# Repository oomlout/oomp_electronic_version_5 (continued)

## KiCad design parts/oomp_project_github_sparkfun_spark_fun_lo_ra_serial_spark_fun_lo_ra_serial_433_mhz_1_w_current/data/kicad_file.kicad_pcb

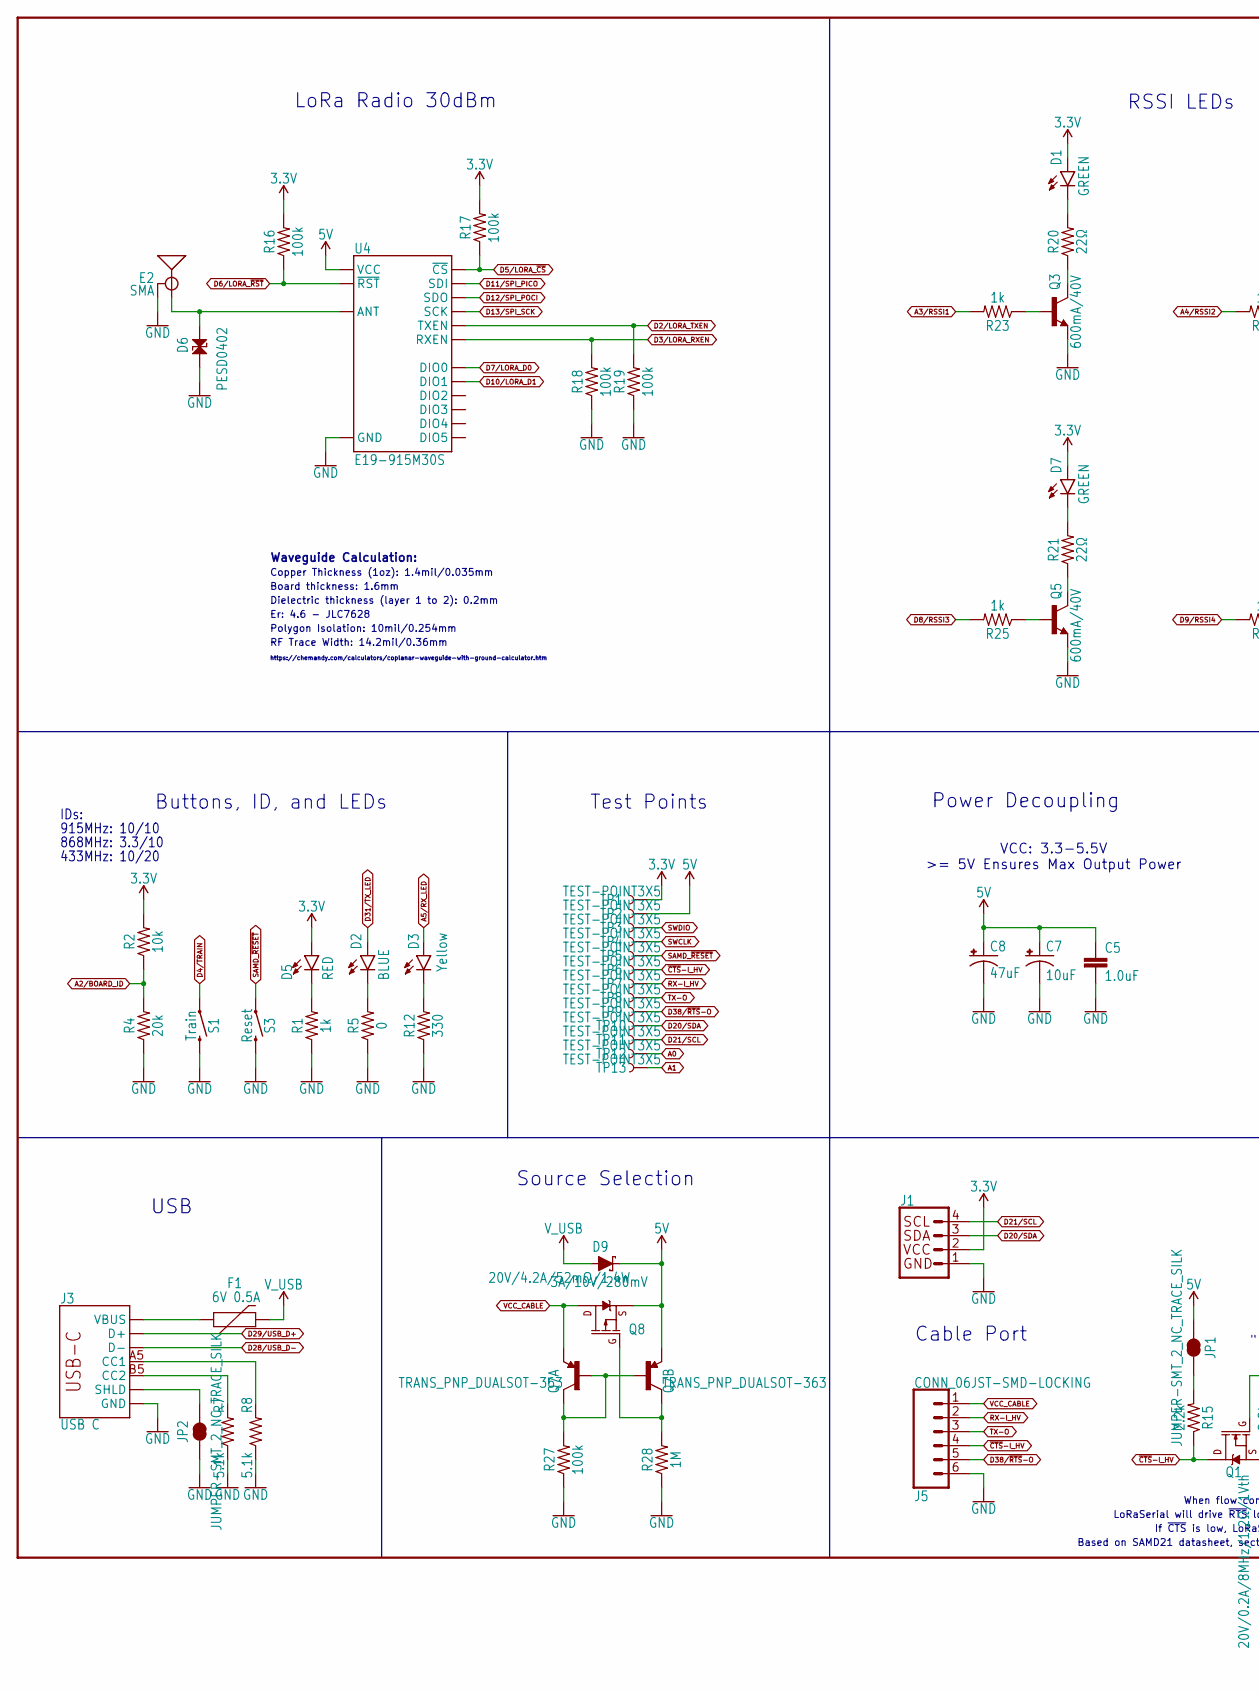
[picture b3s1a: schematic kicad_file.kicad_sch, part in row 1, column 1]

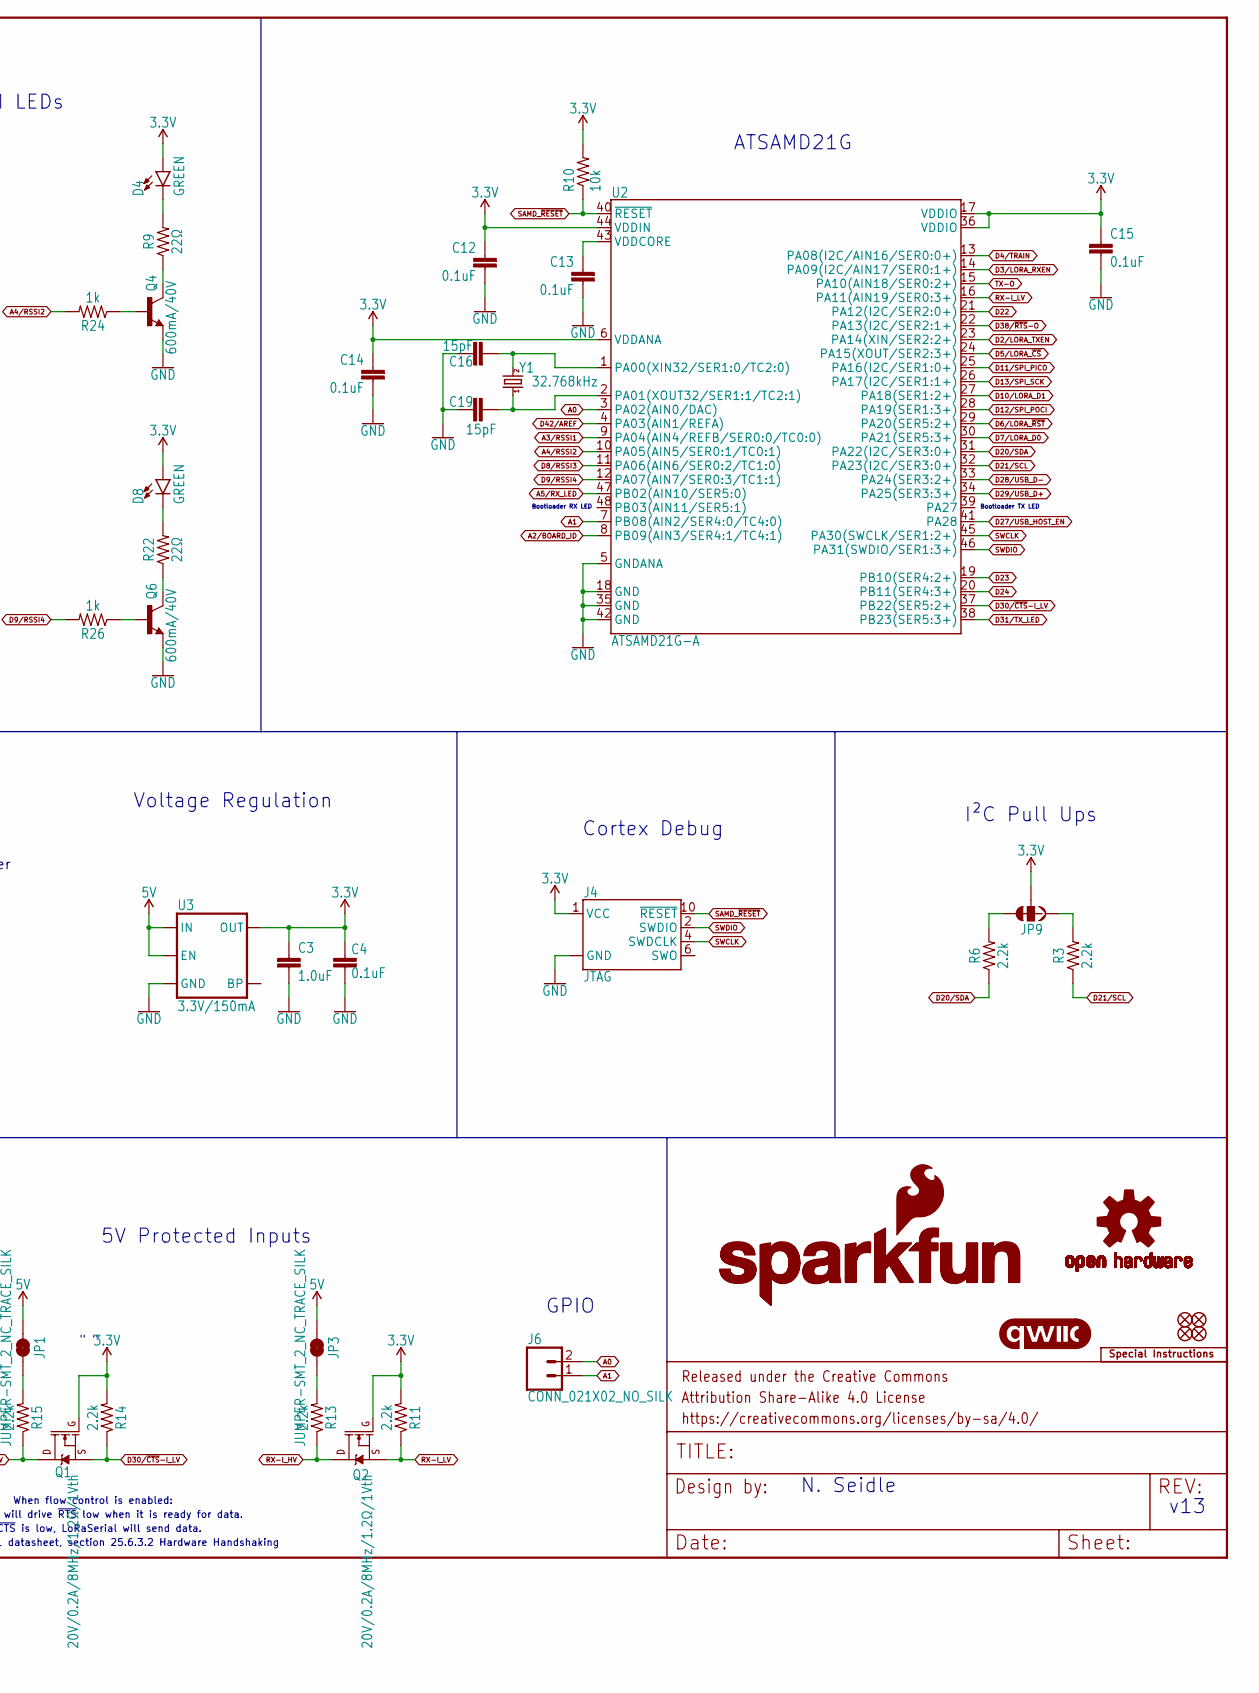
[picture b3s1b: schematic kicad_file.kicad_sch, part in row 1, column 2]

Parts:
C3, C5: 1.0uF; 0603
C4, C12, C13, C14, C15: 0.1uF; 0603
C7: 10uF; EIA3216
C8: 47uF; EIA3528
C16, C19: 15pF; 0603
D1, D4, D7, D8: GREEN; LED-0603
D2: BLUE; LED-0603
D3: Yellow; LED-0603
D5: RED; LED-0603
D6: PESD0402; 0402-TIGHT
D9: 3A/10V/280mV; SOD-323
E2: SMA; SMA-EDGE
F1: 6V 0.5A; 0805
FID1, FID2, FID3, FID4: FIDUCIAL1X2; FIDUCIAL-1X2
FRAME3: FRAME-LEDGER; CREATIVE_COMMONS
J1: QWIIC_RIGHT_ANGLE; JST04_1MM_RA
J3: USB C; USB-C-16P
J4: JTAG; 2X5-PTH-1.27MM-NO_SILK
J5: CONN_06JST-SMD-LOCKING; JST-6-SMD-1.25MM-LOCKING
J6: CONN_021X02_NO_SILK; 1X02_NO_SILK
JP1, JP2, JP3: JUMPER-SMT_2_NC_TRACE_SILK; SMT-JUMPER_2_NC_TRACE_SILK
JP9: JUMPER-SMT_3_2-NC_TRACE_SILK; SMT-JUMPER_3_2-NC_TRACE_SILK
LOGO1: SPECIAL_INSTRUCTIONS-ORDERING; ORDERING_INSTRUCTIONS
LOGO2: SFE_LOGO_NAME_FLAME9_MM; SFE_LOGO_NAME_FLAME_9MM
LOGO3: QWIIC_LOGO_CONNECTOR; QWIIC_5.5MM
LOGO4: OSHW-LOGOMINI; OSHW-LOGO-MINI
LOGO5: SFE_LOGO_NAME9_MM; SFE_LOGO_NAME_9MM
Q1, Q2: 20V/0.2A/8MHz/1.2Ω/1Vth; SOT-416FL
Q3, Q4, Q5, Q6: 600mA/40V; SOT23-3
Q7: TRANS_PNP_DUALSOT-363; SOT363_PHILIPS
Q8: 20V/4.2A/52mΩ/1.4W; SOT23-3
R1, R23, R24, R25, R26: 1k; 0603
R2, R10: 10k; 0603
R3, R6, R11, R13, R14, R15: 2.2k; 0603
R4: 20k; 0603
R5: 0; 0603
R7, R8: 5.1k; 0603
R9, R20, R21, R22: 22Ω; 0603
R12: 330; 0603
R16, R17, R18, R19, R27: 100k; 0603
R28: 1M; 0603
S1: Train; TACTILE_SWITCH_SMD_RIGHT_ANGLE
S3: Reset; TACTILE_SWITCH_SMD_5.2MM
TP1, TP2, TP3, TP4, TP5, TP6, TP7, TP8, TP9, TP10, TP11, TP12, TP13: TEST-POINT3X5; PAD.03X.05
U2: ATSAMD21G-A; TQFP-48
U3: 3.3V/150mA; SOT23-5
U4: E19-915M30S; E19-433M30S
Y1: 32.768kHz; CRYSTAL-SMD-3.2X1.5MM

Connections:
3.3V: C3.1, C4.2, C12.1, C14.1, C15.1, D1.A, D4.A, D5.A, D7.A, D8.A, J1.2, J4.1 (VCC), JP9.2, Q1.1 (G), Q2.1 (G), R2.2, R10.2, R11.2, R14.2, R16.2, R17.2, TP1.1, U2.6 (VDDANA), U2.17 (VDDIO), U2.36 (VDDIO), U2.44 (VDDIN), U3.5 (OUT)
5V: C5.1, C7.+, C8.A (+), D9.C, JP1.2, JP3.2, Q7.4 (E), Q8.2 (S), TP2.1, U3.1 (IN), U3.3 (EN), U4.11 (VCC)
A0: J6.2, TP12.1, U2.3 (PA02(AIN0/DAC))
A1: J6.1, TP13.1, U2.7 (PB08(AIN2/SER4:0/TC4:0))
A2/BOARD_ID: R2.1, R4.2, U2.8 (PB09(AIN3/SER4:1/TC4:1))
A3/RSSI1: R23.2, U2.9 (PA04(AIN4/REFB/SER0:0/TC0:0))
A4/RSSI2: R24.2, U2.10 (PA05(AIN5/SER0:1/TC0:1))
A5/RX_LED: D3.A, U2.47 (PB02(AIN10/SER5:0))
CC1: J3.A5 (CC1), R8.2
CC2: J3.B5 (CC2), R7.2
D2/LORA_TXEN: R19.2, U2.23 (PA14(XIN/SER2:2+)), U4.16 (TXEN)
D3/LORA_RXEN: R18.2, U2.14 (PA09(I2C/AIN17/SER0:1+)), U4.17 (RXEN)
D4/TRAIN: S1.1, U2.13 (PA08(I2C/AIN16/SER0:0+))
D5/LORA_~CS: R17.1, U2.24 (PA15(XOUT/SER2:3+)), U4.15 (~CS)
D6/LORA_~RST: R16.1, U2.29 (PA20(SER5:2+)), U4.8 (~RST)
D7/LORA_D0: U2.30 (PA21(SER5:3+)), U4.7 (DIO0)
D8/RSSI3: R25.2, U2.11 (PA06(AIN6/SER0:2/TC1:0))
D9/RSSI4: R26.2, U2.12 (PA07(AIN7/SER0:3/TC1:1))
D10/LORA_D1: U2.27 (PA18(SER1:2+)), U4.6 (DIO1)
D11/SPI_PICO: U2.25 (PA16(I2C/SER1:0+)), U4.14 (SDI)
D12/SPI_POCI: U2.28 (PA19(SER1:3+)), U4.13 (SDO)
D13/SPI_SCK: U2.26 (PA17(I2C/SER1:1+)), U4.12 (SCK)
D20/SDA: J1.3, R6.1, TP10.1, U2.31 (PA22(I2C/SER3:0+))
D21/SCL: J1.4, R3.1, TP11.1, U2.32 (PA23(I2C/SER3:0+))
D22: U2.21 (PA12(I2C/SER2:0+))
D23: U2.19 (PB10(SER4:2+))
D24: U2.20 (PB11(SER4:3+))
D27/USB_HOST_EN: U2.41 (PA28)
D28/USB_D-: J3.A7 (D-), J3.B7 (D-), U2.33 (PA24(SER3:2+))
D29/USB_D+: J3.A6 (D+), J3.B6 (D+), U2.34 (PA25(SER3:3+))
D30/~CTS-I_LV: Q1.2 (S), R14.1, U2.37 (PB22(SER5:2+))
D31/TX_LED: D2.A, U2.38 (PB23(SER5:3+))
D38/~RTS-O: J5.5, TP9.1, U2.22 (PA13(I2C/SER2:1+))
D42/AREF: U2.4 (PA03(AIN1/REFA))
GND: C3.2, C4.1, C5.2, C7.-, C8.C (-), C12.2, C13.2, C14.2, C15.2, C16.1, C19.2, D6.1, E2.GND@0 (GND), E2.GND@1 (GND), E2.GND@2 (GND), E2.GND@3 (GND), J1.1, J3.GND, J3.GND2 (GND), J4.3 (GND), J4.5 (GND), J4.9 (GND), J5.6, JP2.1, Q3.2 (E), Q4.2 (E), Q5.2 (E), Q6.2 (E), R1.1, R4.1, R5.1, R7.1, R8.1, R12.1, R18.1, R19.1, R27.1, R28.1, S1.2, S3.3 (2), S3.4 (2), U2.5 (GNDANA), U2.18 (GND), U2.35 (GND), U2.42 (GND), U3.2 (GND), U4.1 (GND), U4.9 (GND), U4.10 (GND), U4.18 (GND), U4.20 (GND), U4.21 (GND), U4.22 (GND)
LORA_ANT: D6.2, E2.SIG (SIGNAL), U4.19 (ANT)
unnamed: C19.1, U2.2 (PA01(XOUT32/SER1:1/TC2:1)), Y1.P$1 (1)
unnamed: C16.2, U2.1 (PA00(XIN32/SER1:0/TC2:0)), Y1.P$2 (2)
unnamed: D3.C, R12.2
unnamed: D2.C, R5.2
unnamed: JP3.1, R13.2
unnamed: JP1.1, R15.2
unnamed: D5.C, R1.2
unnamed: D4.C, R9.2
unnamed: D1.C, R20.2
unnamed: D7.C, R21.2
unnamed: D8.C, R22.2
unnamed: Q3.3 (C), R20.1
unnamed: Q3.1 (B), R23.1
unnamed: Q4.3 (C), R9.1
unnamed: Q4.1 (B), R24.1
unnamed: Q5.3 (C), R21.1
unnamed: Q5.1 (B), R25.1
unnamed: Q6.3 (C), R22.1
unnamed: Q6.1 (B), R26.1
unnamed: J3.SHLD1 (SHLD), J3.SHLD2 (SHLD), J3.SHLD3 (SHLD), J3.SHLD4 (SHLD), J3.SHLD5 (SHLD), J3.SHLD6 (SHLD), J3.SHLD7 (SHLD), J3.SHLD8 (SHLD), JP2.2
unnamed: Q7.3 (C), Q8.1 (G), R28.2
unnamed: Q7.2 (B), Q7.5 (B), Q7.6 (C), R27.2
RX-I_HV: J5.2, Q2.3 (D), R13.1, TP7.1
RX-I_LV: Q2.2 (S), R11.1, U2.16 (PA11(AIN19/SER0:3+))
SAMD_~RESET: J4.10 (~RESET), R10.1, S3.1, S3.2 (1), TP5.1, U2.40 (~RESET)
SCL_PU1: JP9.1, R3.2
SDA_PU1: JP9.3, R6.2
SWCLK: J4.4 (SWDCLK), TP4.1, U2.45 (PA30(SWCLK/SER1:2+))
SWDIO: J4.2 (SWDIO), TP3.1, U2.46 (PA31(SWDIO/SER1:3+))
TX-O: J5.3, TP8.1, U2.15 (PA10(AIN18/SER0:2+))
VCC_CABLE: J5.1, Q7.1 (E), Q8.3 (D)
VDDCORE: C13.1, U2.43 (VDDCORE)
VUSB: F1.1, J3.VBUS1 (VBUS), J3.VBUS2 (VBUS)
V_USB: D9.A, F1.2
~CTS-I_HV: J5.4, Q1.3 (D), R15.1, TP6.1

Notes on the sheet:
ATSAMD21G
Er: 4.6 - JLC7628
Buttons, ID, and LEDs
https://chemandy.com/calculators/coplanar-waveguide-with-ground-calculator.htm
Voltage Regulation
LoRaSerial will drive ~{RTS} low when it is ready for data.
Cable Port
Power Decoupling
N. Seidle
Based on SAMD21 datasheet, section 25.6.3.2 Hardware Handshaking
I²C Pull Ups
When flow control is enabled:
Dielectric thickness (layer 1 to 2): 0.2mm
v13
RSSI LEDs
RF Trace Width: 14.2mil/0.36mm
LoRa Radio 30dBm
Copper Thickness (1oz): 1.4mil/0.035mm
USB
Bootloader TX LED
Bootloader RX LED
433MHz: 10/20
GPIO
Polygon Isolation: 10mil/0.254mm
Source Selection
VCC: 3.3-5.5V >= 5V Ensures Max Output Power
915MHz: 10/10
Test Points
Cortex Debug
Waveguide Calculation:
" "
Board thickness: 1.6mm
If ~{CTS} is low, LoRaSerial will send data.
IDs:
5V Protected Inputs
868MHz: 3.3/10

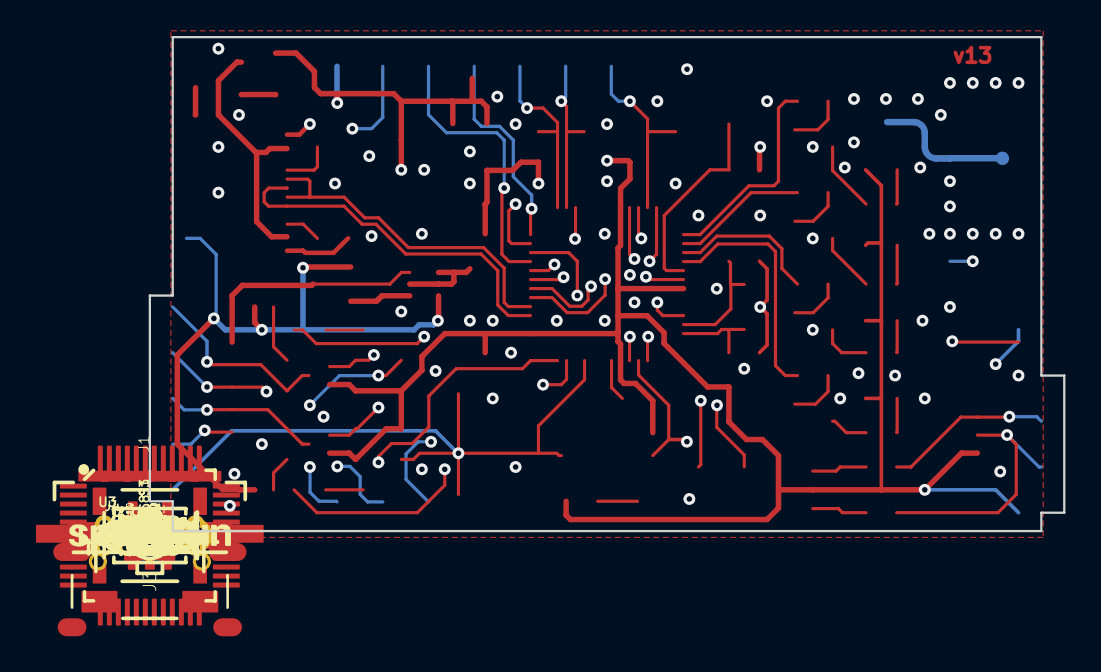
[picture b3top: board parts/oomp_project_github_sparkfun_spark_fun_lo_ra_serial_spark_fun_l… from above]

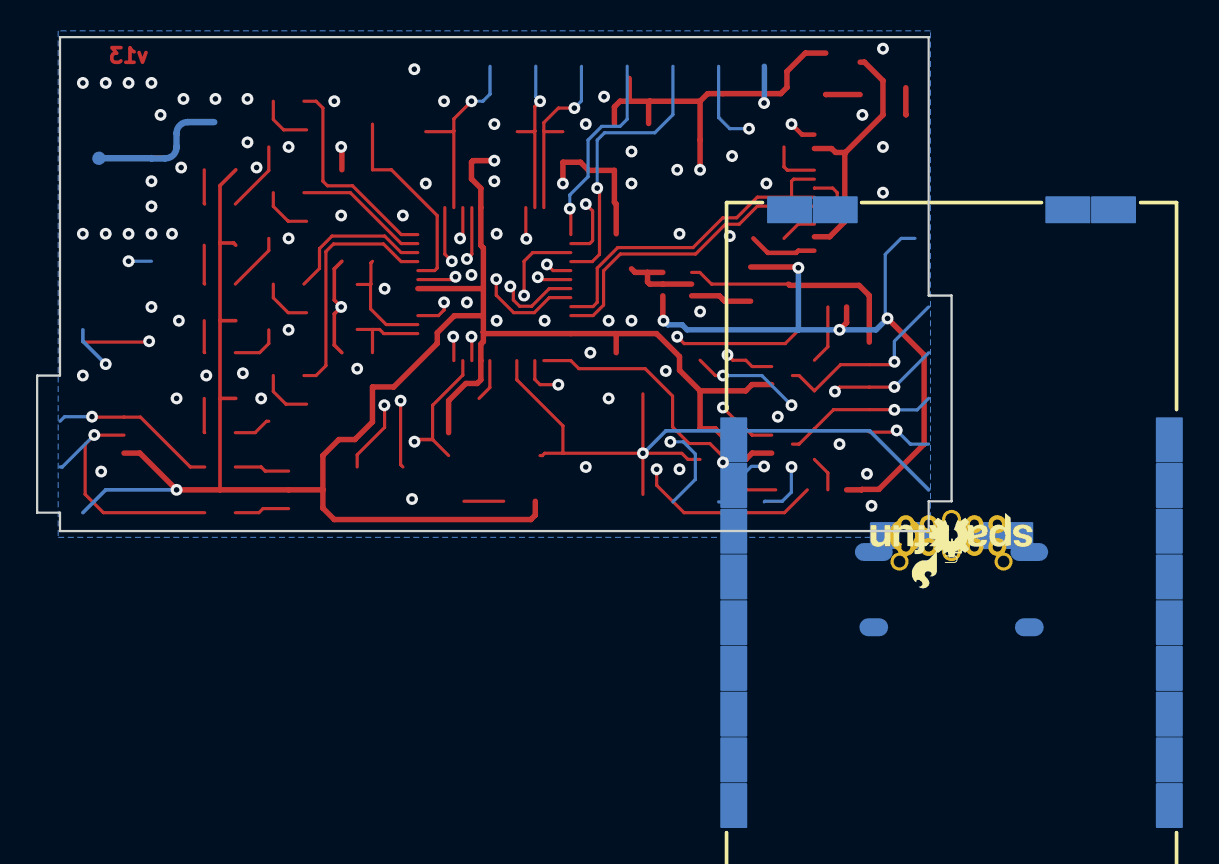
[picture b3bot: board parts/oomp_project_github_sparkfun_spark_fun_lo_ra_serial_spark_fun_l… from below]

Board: 4 copper layers, 50.8 x 27.4 mm, 118 parts (20 on the bottom side), 66 nets.

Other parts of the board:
U$1: 1W1
U$2: RESET0
U$4: TRAIN0
U$5: RADIO2
U$6: 01
U$7: PWR0
U$8: 433MHZ0
U$9: ANTENNA1
U$10: RX1
U$11: TX0
U$12: #0
U$13: #1
U$14: R3
U$15: T2
U$16: C0
U$17: R1
U$18: LORASERIAL0
U$19: C50
U$20: R50
U$21: RSSI0
U$22: 10
U$23: SH0

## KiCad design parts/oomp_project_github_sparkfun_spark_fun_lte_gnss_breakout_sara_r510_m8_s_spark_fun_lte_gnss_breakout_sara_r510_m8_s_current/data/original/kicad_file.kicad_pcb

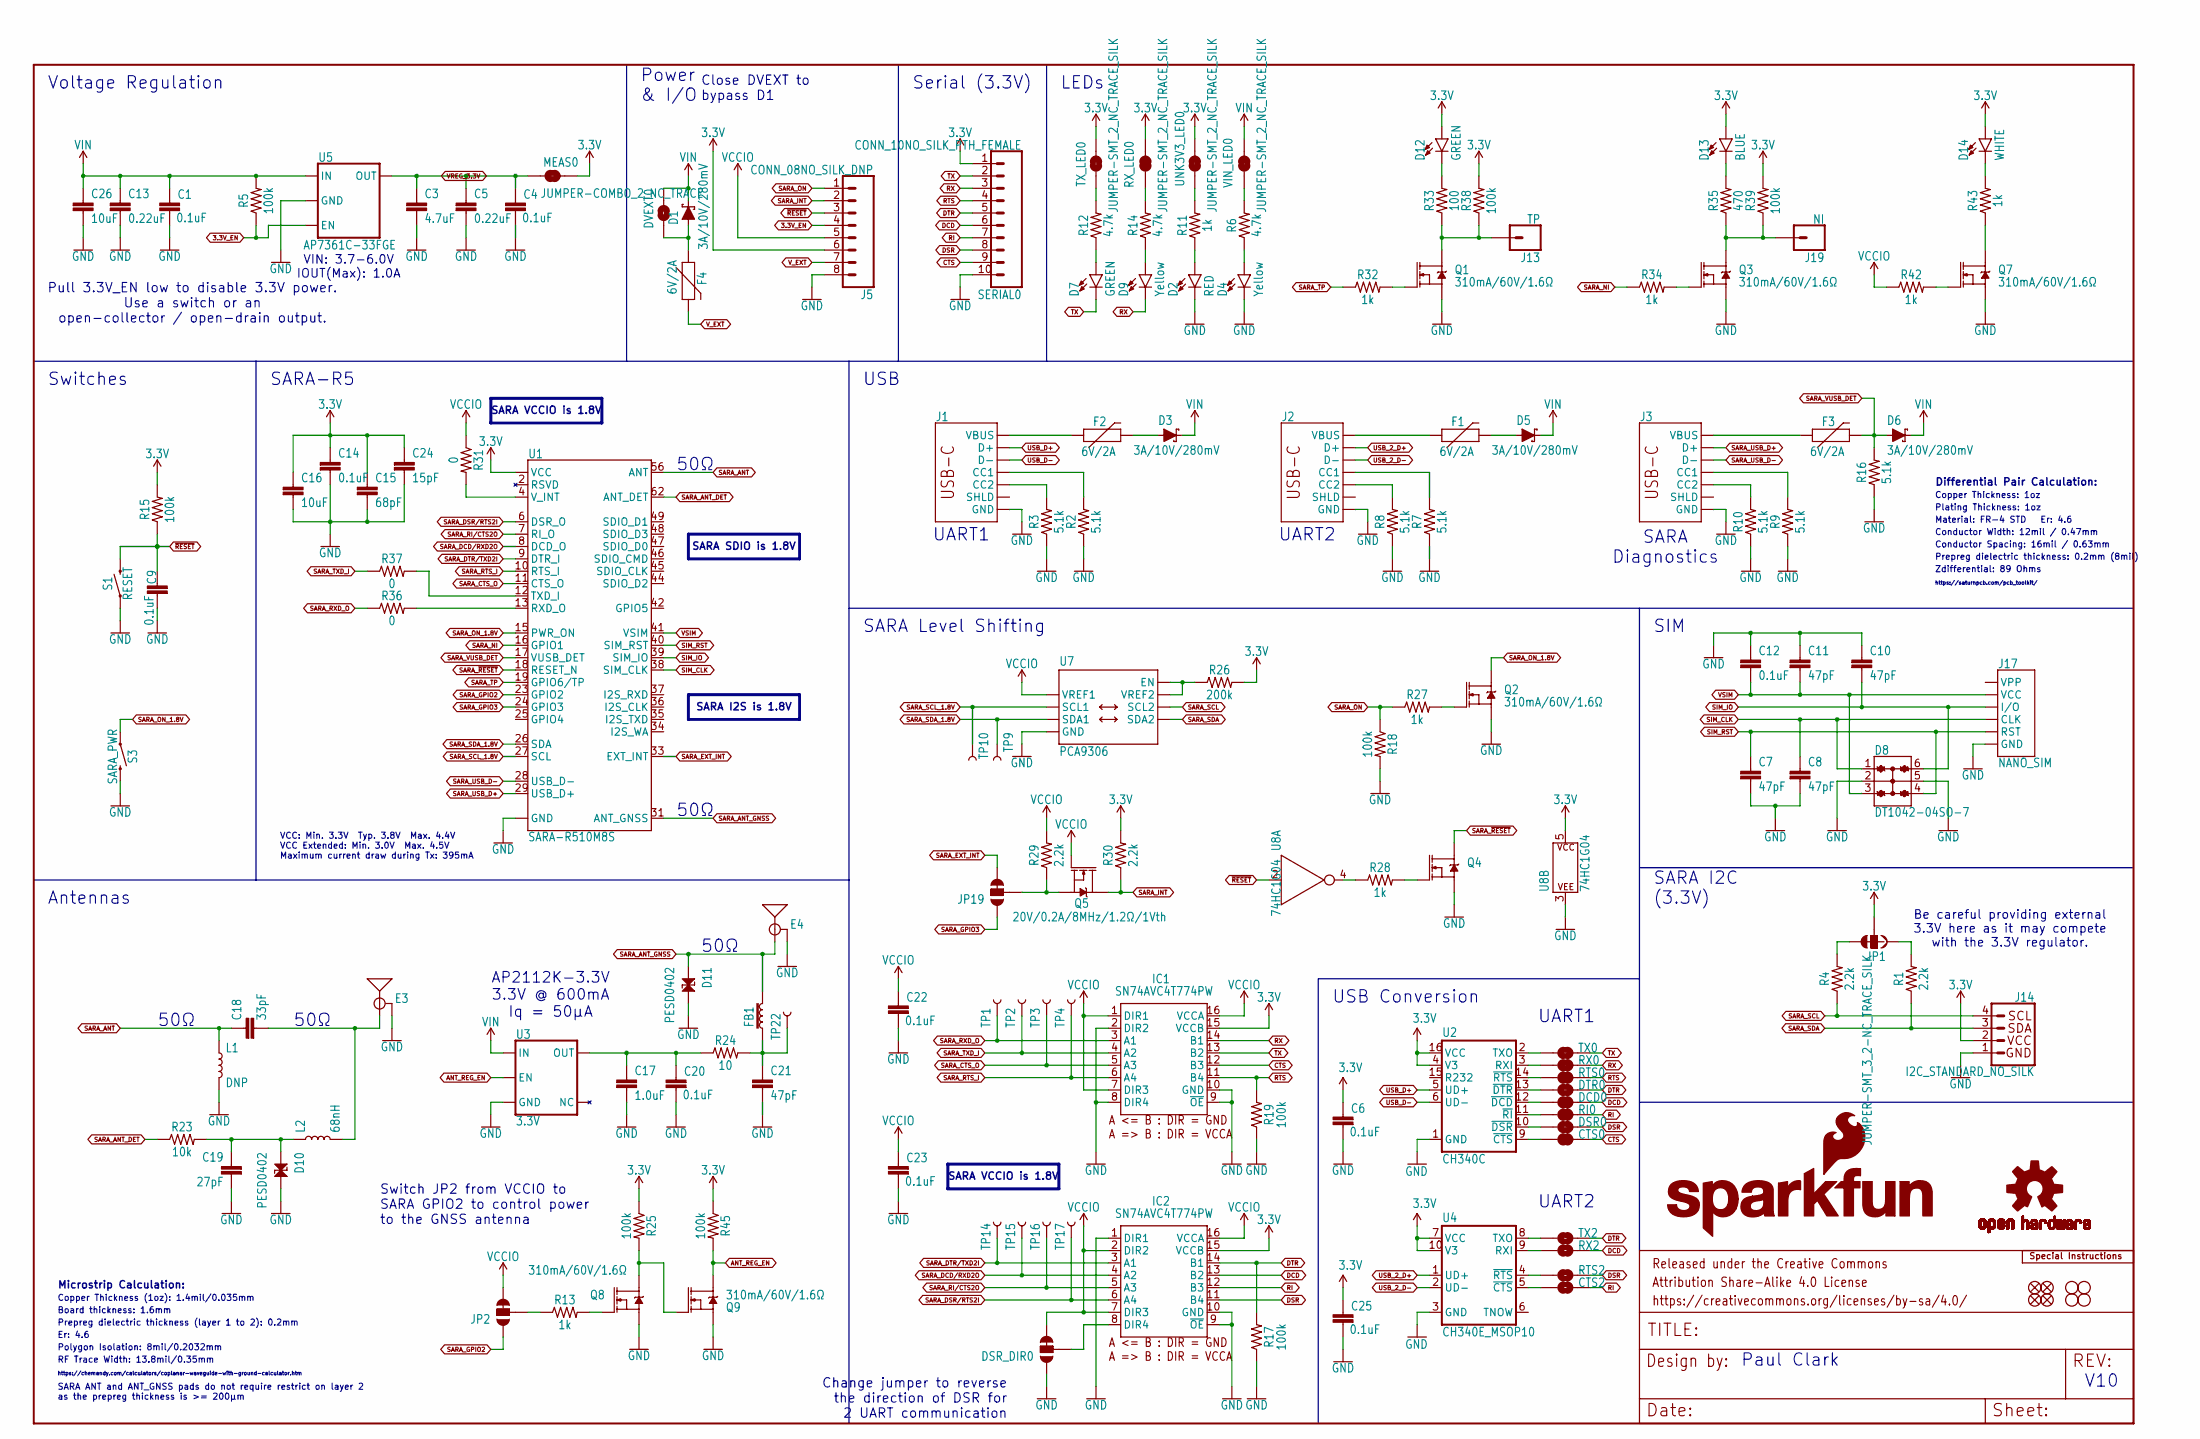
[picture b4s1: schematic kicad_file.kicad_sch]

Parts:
C1, C4, C6, C9, C12, C14, C20, C22, C23, C25: 0.1uF; 0603
C3: 4.7uF; 0603
C5, C13: 0.22uF; 0603
C7, C8, C10, C11, C21: 47pF; 0603
C15: 68pF; 0603
C16: 10uF; 0603
C17: 1.0uF; 0603
C18: 33pF; 0402-TIGHT
C19: 27pF; 0402
C24: 15pF; 0603
C26: 10uF; 0805
CTS0: JUMPER-SMT_2_NC_TRACE_SILK; SMT-JUMPER_2_NC_TRACE_SILK
CTS2: JUMPER-SMT_2_NO_SILK; SMT-JUMPER_2_NO_SILK
D1, D3, D5, D6: 3A/10V/280mV; SOD-323
D2: RED; LED-0603
D4, D9: Yellow; LED-0603
D7, D12: GREEN; LED-0603
D8: DT1042-04SO-7; SOT23-6L
D10, D11: PESD0402; 0402; MOUSE_PART 650-PESD0402-140; DIGIKEY_PART PESD0402-140CT-ND
D13: BLUE; LED-0603
D14: WHITE; LED-0603
DCD0: JUMPER-SMT_2_NC_TRACE_SILK; SMT-JUMPER_2_NC_TRACE_SILK
DSR0: JUMPER-SMT_2_NC_TRACE_SILK; SMT-JUMPER_2_NC_TRACE_SILK
DSR_DIR0: JUMPER-SMT_3_1-NC_TRACE_SILK; SMT-JUMPER_3_1-NC_TRACE_SILK
DTR0: JUMPER-SMT_2_NC_TRACE_SILK; SMT-JUMPER_2_NC_TRACE_SILK
DVEXT0: JUMPER-SMT_2_NO_SILK; SMT-JUMPER_2_NO_SILK
E3, E4: ANTENNA-SMA-GROUNDEDEDGE_SMA_SMD; SMA-EDGE-SMD
F1, F2, F3, F4: 6V/2A; 1210
FB1: 30Ω/1.8A; 0603
FD1, FD2, FD3, FD4: FIDUCIALUFIDUCIAL; FIDUCIAL-MICRO
FRAME1: FRAME-LEDGER; CREATIVE_COMMONS
H1, H2, H3, H4: STAND-OFF
IC1, IC2: SN74AVC4T774PW; SOP65P640X120-16N
J1, J2, J3: USB_C_4-LAYER_PADS; USB-C-16P_4LAYER-PADS
J5: CONN_08NO_SILK_DNP; 1X08_NO_SILK
J13: TP; 1X01_NO_SILK
J14: I2C_STANDARD_NO_SILK; 1X04_NO_SILK
J17: NANO_SIM; NANO_SIM_WURTH_693043020611
J19: NI; 1X01_NO_SILK
JP1: JUMPER-SMT_3_2-NC_TRACE_SILK; SMT-JUMPER_3_2-NC_TRACE_SILK
JP2, JP19: JUMPER-SMT_3_1-NC_TRACE_SILK; SMT-JUMPER_3_1-NC_TRACE_SILK
L1: DNP; 0402_COILCRAFT
L2: 68nH; 0402_COILCRAFT; MOUSER_PART 81-LQG15HS68NJ02D; DIGIKEY_PART 490-2633-1-ND
LOGO1: SFE_LOGO_NAME_FLAME.1_INCH; SFE_LOGO_NAME_FLAME_.1
LOGO3: OSHW-LOGOMINI; OSHW-LOGO-MINI
LOGO5: SPECIAL_INSTRUCTIONS-ORDERING; ORDERING_INSTRUCTIONS
MEAS0: JUMPER-COMBO_2_NC_TRACE; COMBO-JUMPER_2_NC_TRACE
Q1, Q2, Q3, Q4, Q7, Q8, Q9: 310mA/60V/1.6Ω; SOT323
Q5: 20V/0.2A/8MHz/1.2Ω/1Vth; SOT-416FL
R1, R4, R29, R30: 2.2k; 0603
R2, R3, R7, R8, R9, R10, R16: 5.1k; 0603
R5, R15, R17, R18, R19, R25, R38, R39, R45: 100k; 0603
R6, R12, R14: 4.7k; 0603
R11, R13, R27, R28, R32, R34, R42, R43: 1k; 0603
R23: 10k; 0603
R24: 10; 0603
R26: 200k; 0603
R31, R36, R37: 0; 0603
R33: 100; 0603
R35: 470; 0603
RI0: JUMPER-SMT_2_NC_TRACE_SILK; SMT-JUMPER_2_NC_TRACE_SILK
RTS0: JUMPER-SMT_2_NC_TRACE_SILK; SMT-JUMPER_2_NC_TRACE_SILK
RTS2: JUMPER-SMT_2_NO_SILK; SMT-JUMPER_2_NO_SILK
RX0: JUMPER-SMT_2_NC_TRACE_SILK; SMT-JUMPER_2_NC_TRACE_SILK
RX2: JUMPER-SMT_2_NO_SILK; SMT-JUMPER_2_NO_SILK
RX_LED0: JUMPER-SMT_2_NC_TRACE_SILK; SMT-JUMPER_2_NC_TRACE_SILK
S1: RESET; TACTILE_SWITCH_SMD_5.2MM
S3: SARA_PWR; TACTILE_SWITCH_SMD_5.2MM
SERIAL0: CONN_10NO_SILK_PTH_FEMALE; 1X10_NO_SILK
TP1, TP2, TP3, TP4, TP9, TP10, TP14, TP15, TP16, TP17, TP22: TEST-POINT3; PAD.03X.03
TX0: JUMPER-SMT_2_NC_TRACE_SILK; SMT-JUMPER_2_NC_TRACE_SILK
TX2: JUMPER-SMT_2_NO_SILK; SMT-JUMPER_2_NO_SILK
TX_LED0: JUMPER-SMT_2_NC_TRACE_SILK; SMT-JUMPER_2_NC_TRACE_SILK
U1: SARA-R510M8S; SARA-LGA
U2: CH340C; SO016
U3: 3.3V; SOT23-5
U4: CH340E_MSOP10; MSOP10
U5: AP7361C-33FGE; UDFN-8
U7: PCA9306; VSSOP_8PIN
U8: 74HC1G04; SOT353
UNK3V3_LED0: JUMPER-SMT_2_NC_TRACE_SILK; SMT-JUMPER_2_NC_TRACE_SILK
VIN_LED0: JUMPER-SMT_2_NC_TRACE_SILK; SMT-JUMPER_2_NC_TRACE_SILK

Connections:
3.3V: C6.1, C14.1, C15.1, C16.1, C24.1, C25.1, D12.A, D13.A, D14.A, IC1.15 (VCCB), IC2.15 (VCCB), J5.6, J14.2, JP1.2, MEAS0.2, MEAS0.4 (2), R15.2, R25.1, R26.2, R30.2, R38.2, R39.2, R45.1, RX_LED0.2, SERIAL0.1, TX_LED0.2, U1.51 (VCC), U1.52 (VCC), U1.53 (VCC), U2.4 (V3), U2.16 (VCC), U4.7 (VCC), U4.10 (V3), U8.5 (P$V+), UNK3V3_LED0.2
3.3V_EN: J5.4, R5.1, U5.5 (EN)
ANT_REG_EN: Q9.3 (D), R45.2, U3.3 (EN)
CTS: CTS0.2, IC1.12 (B3), SERIAL0.9
DCD: DCD0.2, IC2.13 (B2), RX2.2, SERIAL0.6
DSR: DSR0.2, IC2.11 (B4), RTS2.2, SERIAL0.8
DTR: DTR0.2, IC2.14 (B1), R17.2, SERIAL0.5, TX2.2
GND: C1.2, C3.2, C4.2, C5.2, C6.2, C7.2, C8.2, C9.2, C10.1, C11.1, C12.1, C13.2, C14.2, C15.2, C16.2, C17.2, C19.2, C20.2, C21.2, C22.2, C23.2, C24.2, C25.2, C26.2, D2.C, D4.C, D8.2, D8.5, D10.2, D11.2, DSR_DIR0.1, E3.GND@0 (GND), E3.GND@1 (GND), E4.GND@0 (GND), E4.GND@1 (GND), IC1.2 (DIR2), IC1.8 (DIR4), IC1.9 (~OE), IC1.10 (GND), IC2.1 (DIR1), IC2.9 (~OE), IC2.10 (GND), J1.GND, J1.GND2 (GND), J2.GND, J2.GND2 (GND), J3.GND, J3.GND2 (GND), J5.8, J14.1, J17.C5 (GND), L1.P$2 (2), Q1.2 (S), Q2.2 (S), Q3.2 (S), Q4.2 (S), Q7.2 (S), Q8.2 (S), Q9.2 (S), R2.1, R3.1, R7.1, R8.1, R9.1, R10.1, R16.1, R17.1, R18.2, R19.1, S1.1, S1.2 (1), S3.3 (2), S3.4 (2), SERIAL0.10, U1.1 (GND), U1.3 (GND), U1.5 (GND), U1.14 (GND), U1.20 (GND), U1.21 (GND), U1.22 (GND), U1.30 (GND), U1.32 (GND), U1.43 (GND), U1.50 (GND), U1.54 (GND), U1.55 (GND), U1.57 (GND), U1.58 (GND), U1.59 (GND), U1.60 (GND), U1.61 (GND), U1.63 (GND), U1.64 (GND), U1.65 (GND), U1.66 (GND), U1.67 (GND), U1.68 (GND), U1.69 (GND), U1.70 (GND), U1.71 (GND), U1.72 (GND), U1.73 (GND), U1.74 (GND), U1.75 (GND), U1.76 (GND), U1.77 (GND), U1.78 (GND), U1.79 (GND), U1.80 (GND), U1.81 (GND), U1.82 (GND), U1.83 (GND), U1.84 (GND), U1.85 (GND), U1.86 (GND), U1.87 (GND), U1.88 (GND), U1.89 (GND), U1.90 (GND), U1.91 (GND), U1.92 (GND), U1.93 (GND), U1.94 (GND), U1.95 (GND), U1.96 (GND), U2.1 (GND), U3.2 (GND), U4.3 (GND), U5.4 (GND), U5.EP (GND), U7.P1 (GND), U8.3 (P$V-)
unnamed: R6.2, VIN_LED0.1
unnamed: JP1.3, R4.2
unnamed: JP1.1, R1.2
unnamed: D3.A, F2.2
unnamed: J2.A5 (CC1), R7.2
unnamed: R11.2, UNK3V3_LED0.1
unnamed: D2.A, R11.1
unnamed: D4.A, R6.1
unnamed: J2.B5 (CC2), R8.2
unnamed: J1.A5 (CC1), R2.2
unnamed: J1.B5 (CC2), R3.2
unnamed: D5.A, F1.2
unnamed: F1.1, J2.VBUS1 (VBUS), J2.VBUS2 (VBUS)
unnamed: J3.A5 (CC1), R9.2
unnamed: C18.2, E3.SIG (SIGNAL), L2.P$2 (2)
unnamed: C19.1, D10.1, L2.P$1 (1), R23.2
unnamed: J3.B5 (CC2), R10.2
unnamed: F3.1, J3.VBUS1 (VBUS), J3.VBUS2 (VBUS)
unnamed: F2.1, J1.VBUS1 (VBUS), J1.VBUS2 (VBUS)
unnamed: TX0.1, U2.2 (TXO)
unnamed: RX0.1, U2.3 (RXI)
unnamed: R26.1, U7.P7 (VREF2), U7.P8 (EN)
unnamed: DSR_DIR0.2, IC2.8 (DIR4)
unnamed: C17.1, C20.1, R24.1, U3.5 (OUT)
unnamed: C21.1, FB1.1, R24.2, TP22.P$1
unnamed: Q2.1 (G), R27.2
unnamed: Q4.1 (G), R28.2
unnamed: R28.1, U8.4 (Y)
unnamed: RTS0.1, U2.14 (~RTS)
unnamed: DTR0.1, U2.13 (~DTR)
unnamed: R31.2, U1.4 (V_INT)
unnamed: Q1.1 (G), R32.2
unnamed: J13.1, Q1.3 (D), R33.1, R38.1
unnamed: D12.C, R33.2
unnamed: Q3.1 (G), R34.2
unnamed: J19.1, Q3.3 (D), R35.1, R39.1
unnamed: D13.C, R35.2
unnamed: R36.2, U1.13 (RXD_O)
unnamed: R37.2, U1.12 (TXD_I)
unnamed: Q8.1 (G), R13.2
unnamed: DCD0.1, U2.12 (~DCD)
unnamed: Q8.3 (D), Q9.1 (G), R25.2
unnamed: JP19.2, Q5.2 (S), R29.1
unnamed: RI0.1, U2.11 (~RI)
unnamed: DSR0.1, U2.10 (~DSR)
unnamed: CTS0.1, U2.9 (~CTS)
unnamed: Q7.1 (G), R42.2
unnamed: TX2.1, U4.8 (TXO)
unnamed: D14.C, R43.2
unnamed: RX2.1, U4.9 (RXI)
unnamed: RTS2.1, U4.4 (~RTS)
unnamed: CTS2.1, U4.5 (~CTS)
unnamed: R12.2, TX_LED0.1
unnamed: D7.A, R12.1
unnamed: R14.2, RX_LED0.1
unnamed: D9.A, R14.1
unnamed: D1.A, DVEXT0.1, F4.1
unnamed: JP2.2, R13.1
RI: CTS2.2, IC2.12 (B3), RI0.2, SERIAL0.7
RTS: IC1.11 (B4), R19.2, RTS0.2, SERIAL0.4
RX: D9.C, IC1.14 (B1), RX0.2, SERIAL0.3
SARA_ANT: C18.1, L1.P$1 (1), U1.56 (ANT)
SARA_ANT_DET: R23.1, U1.62 (ANT_DET)
SARA_ANT_GNSS: D11.1, E4.SIG (SIGNAL), FB1.2, U1.31 (ANT_GNSS)
SARA_CTS_O: IC1.5 (A3), TP3.P$1, U1.11 (CTS_O)
SARA_DCD/RXD2O: IC2.4 (A2), TP15.P$1, U1.8 (DCD_O)
SARA_DSR/RTS2I: IC2.6 (A4), TP17.P$1, U1.6 (DSR_O)
SARA_DTR/TXD2I: IC2.3 (A1), TP14.P$1, U1.9 (DTR_I)
SARA_EXT_INT: JP19.3, U1.33 (EXT_INT)
SARA_GPIO2: JP2.1, U1.23 (GPIO2)
SARA_GPIO3: JP19.1, U1.24 (GPIO3)
SARA_INT: J5.2, Q5.3 (D), R30.1
SARA_NI: R34.1, U1.16 (GPIO1)
SARA_ON: J5.1, R18.1, R27.1
SARA_ON_1.8V: Q2.3 (D), S3.1, S3.2 (1), U1.15 (PWR_ON)
SARA_RI/CTS2O: IC2.5 (A3), TP16.P$1, U1.7 (RI_O)
SARA_RTS_I: IC1.6 (A4), TP4.P$1, U1.10 (RTS_I)
SARA_RXD_O: IC1.3 (A1), R36.1, TP1.P$1
SARA_SCL: J14.4, R4.1, U7.P6 (SCL2)
SARA_SCL_1.8V: TP10.P$1, U1.27 (SCL), U7.P3 (SCL1)
SARA_SDA: J14.3, R1.1, U7.P5 (SDA2)
SARA_SDA_1.8V: TP9.P$1, U1.26 (SDA), U7.P4 (SDA1)
SARA_TP: R32.1, U1.19 (GPIO6/TP)
SARA_TXD_I: IC1.4 (A2), R37.1, TP2.P$1
SARA_USB_D+: J3.A6 (D+), J3.B6 (D+), U1.29 (USB_D+)
SARA_USB_D-: J3.A7 (D-), J3.B7 (D-), U1.28 (USB_D-)
SARA_VUSB_DET: D6.A, F3.2, R16.2, U1.17 (VUSB_DET)
SARA_~ON: Q7.3 (D), R43.1
SARA_~RESET: Q4.3 (D), U1.18 (RESET_N)
SIM_CLK: C8.1, D8.1, J17.C3 (CLK), U1.38 (SIM_CLK)
SIM_IO: C10.2, D8.6, J17.C7 (I/O), U1.39 (SIM_IO)
SIM_RST: C7.1, D8.4, J17.C2 (RST), U1.40 (SIM_RST)
TX: D7.C, IC1.13 (B2), SERIAL0.2, TX0.2
USB_2_D+: J2.A6 (D+), J2.B6 (D+), U4.1 (UD+)
USB_2_D-: J2.A7 (D-), J2.B7 (D-), U4.2 (UD-)
USB_D+: J1.A6 (D+), J1.B6 (D+), U2.5 (UD+)
USB_D-: J1.A7 (D-), J1.B7 (D-), U2.6 (UD-)
VCCIO: C22.1, C23.1, DSR_DIR0.3, IC1.1 (DIR1), IC1.7 (DIR3), IC1.16 (VCCA), IC2.2 (DIR2), IC2.7 (DIR3), IC2.16 (VCCA), J5.5, JP2.3, Q5.1 (G), R29.2, R31.1, R42.1, U7.P2 (VREF1)
VIN: C1.1, C13.1, C26.1, D1.C, D3.C, D5.C, D6.C, DVEXT0.2, R5.2, U3.1 (IN), U5.8 (IN), VIN_LED0.2
VREG_3.3V: C3.1, C4.1, C5.1, MEAS0.1, MEAS0.3 (1), U5.1 (OUT)
VSIM: C11.2, C12.2, D8.3, J17.C1 (VCC), U1.41 (VSIM)
V_EXT: F4.2, J5.7
~RESET: C9.1, J5.3, R15.1, S1.3 (2), S1.4 (2), U8.2 (A)

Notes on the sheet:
Voltage Regulation
SARA ANT and ANT_GNSS pads do not require restrict on layer 2 as the prepreg thickness is >= 200µm
Power & I/O
Er: 4.6
https://saturnpcb.com/pcb_toolkit/
SARA SDIO is 1.8V
Material: FR-4 STD Er: 4.6
50Ω
Serial (3.3V)
Pull 3.3V_EN low to disable 3.3V power. Use a switch or an open-collector / open-drain output.
UART1
Prepreg dielectric thickness: 0.2mm (8mil)
Board thickness: 1.6mm
UART2
Conductor Spacing: 16mil / 0.63mm
USB Conversion
Zdifferential: 89 Ohms
Copper Thickness: 1oz
Be careful providing external 3.3V here as it may compete with the 3.3V regulator.
Antennas
SARA VCCIO is 1.8V
SIM
Prepreg dielectric thickness (layer 1 to 2): 0.2mm
SARA I2C (3.3V)
Paul Clark
SARA-R5
SARA Level Shifting
SARA I2S is 1.8V
SARA Diagnostics
Switch JP2 from VCCIO to SARA GPIO2 to control power to the GNSS antenna
VCC: Min. 3.3V Typ. 3.8V Max. 4.4V VCC Extended: Min. 3.0V Max. 4.5V Maximum current draw during Tx: 395mA
Polygon Isolation: 8mil/0.2032mm
VIN: 3.7-6.0V IOUT(Max): 1.0A
Close DVEXT to bypass D1
Microstrip Calculation:
USB
V10
Plating Thickness: 1oz
Change jumper to reverse the direction of DSR for 2 UART communication
RF Trace Width: 13.8mil/0.35mm

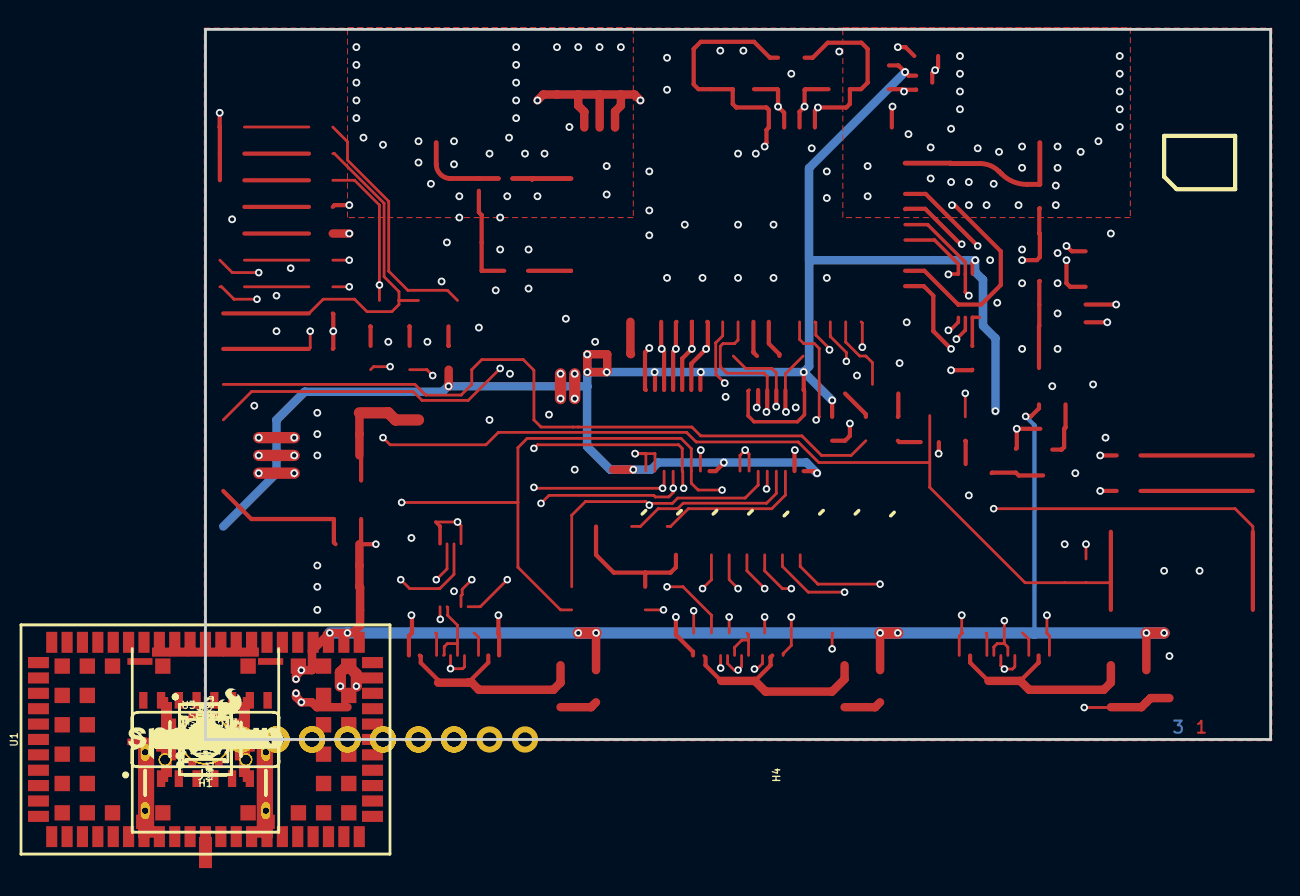
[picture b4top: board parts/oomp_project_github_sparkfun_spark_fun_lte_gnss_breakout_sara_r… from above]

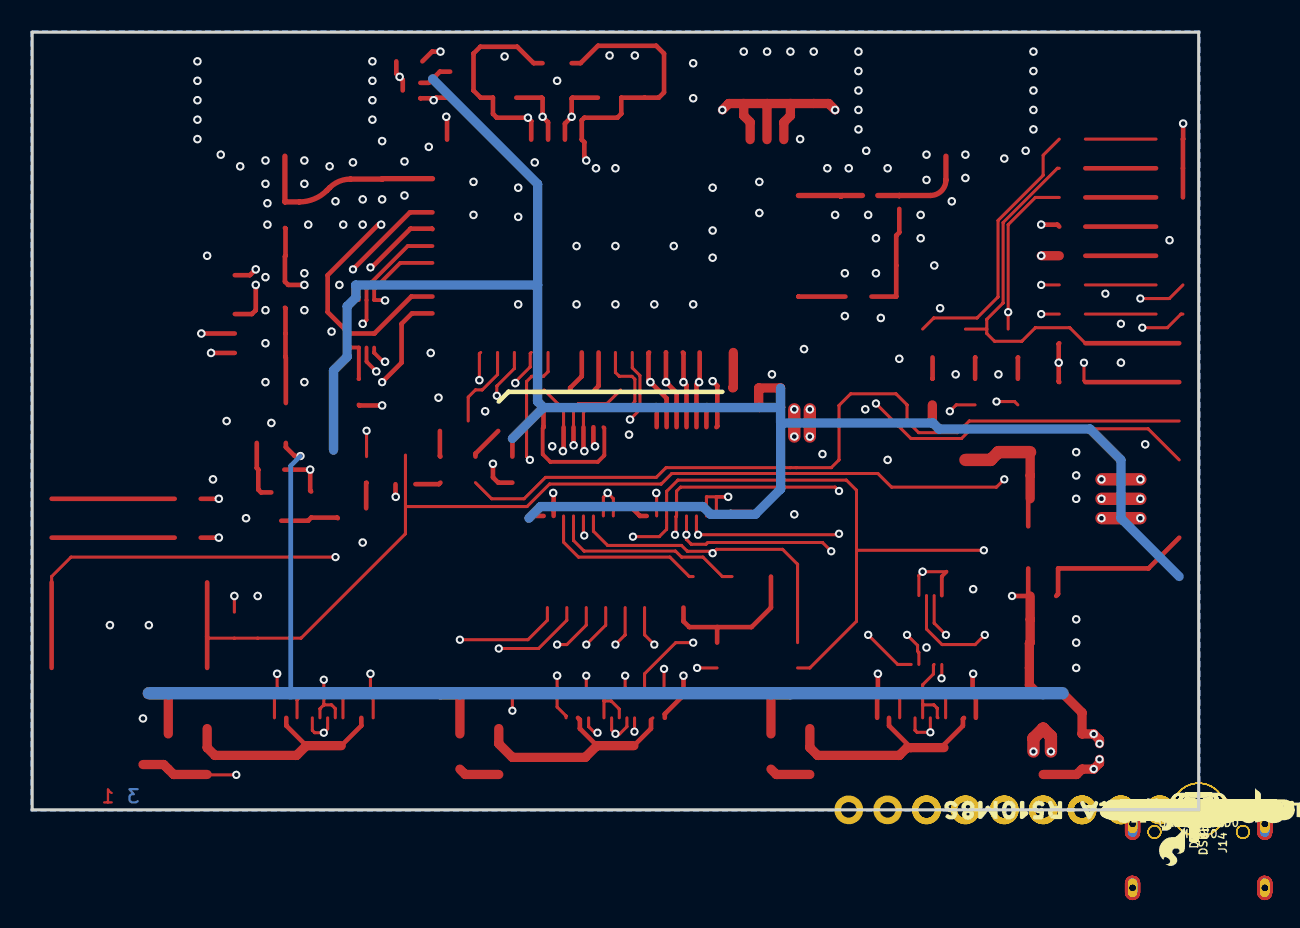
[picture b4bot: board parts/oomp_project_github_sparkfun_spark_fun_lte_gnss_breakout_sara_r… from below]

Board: 4 copper layers, 76.2 x 50.8 mm, 256 parts (90 on the bottom side), 111 nets.

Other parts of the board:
LOGO2: OSHW-LOGOMINI; OSHW-LOGO-MINI
LOGO4: SFE_LOGO_NAME_FLAME.1_INCH; SFE_LOGO_NAME_FLAME_.1
U$1, U$2, U$3, U$11: #3V3#1
U$4: #TX_LED#0
U$5, U$23: #SARA_I�C#0
U$6, U$7: #V_EXT#0
U$8, U$9: #3V3EN#0
U$10, U$13: ##RESET##0
U$12, U$22: #GND#0
U$14: #INT#0
U$15, U$71: #SARA_INT#0
U$16, U$17: #SARA_ON#0
U$18: RX0
U$19, U$87: #MEAS#2
U$20: #RX_LED#0
U$21: TX0
U$24: #TX#0
U$25: #RX#0
U$26, U$27: #SCL#3
U$28: #RTS#0
U$29: #DTR#0
U$30, U$37: #SDA#2
U$31: #DCD#0
U$32: #RI#0
U$33: #DSR#0
U$34: #CTS#0
U$35: #RXD_O#0
U$36: 3V37
U$38: #TXD_I#0
U$39: #CTS_O#0
U$40: #RTS_I#0
U$41: #DTR_TXD2_I#0
U$42: L10
U$43: #DCD_RXD2_O#0
U$44: #RXD2_O#0
U$45: RESET6
U$46: VIN8
U$47: #RI_CTS2_O#0
U$48: #CTS2_O#0
U$49: #DSR_O__RTS2_I#0
U$50: #RTS2_I#0
U$51: #V_EXT_DIODE#0
U$52: #OUT#0
U$53: #IN#0
U$54: #VIN_LED#0
U$55, U$56, U$81, U$82: #GND#4
U$57, U$58: #TP#0
U$59, U$60: #NI#0
U$61: #3V3_LED#0
U$62, U$63: #UART_2#0
U$64, U$65: #UART_1#0
U$66, U$67: #SARA_DIAG#0
U$68, U$80, U$83: #VCCIO#0
U$69: #GPIO2#0
U$70: #ANT_GNSS_PWR#0
U$72: #TXD2_I#0
U$73: LTE_CATEGORY_M10
U$74: LTE_CATEGORY_NB20
U$75: LTE_GNSS_BREAKOUT_#_SARA#R510M8S0
U$76, U$79: #3#3V#0
U$88, U$89: LTE0
U$90: NI0
U$91: TP0
U$99, U$100: GNSS0
U$101: ON0
U$113: SARA_ON0
U$118: #EXT_INT#0
U$119: #GPIO3#0
U$130: NANO0
U$131: SIM0
